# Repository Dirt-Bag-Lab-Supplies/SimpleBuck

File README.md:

# SimpleBuck
Simple buck-converter with selectable output voltage and current.

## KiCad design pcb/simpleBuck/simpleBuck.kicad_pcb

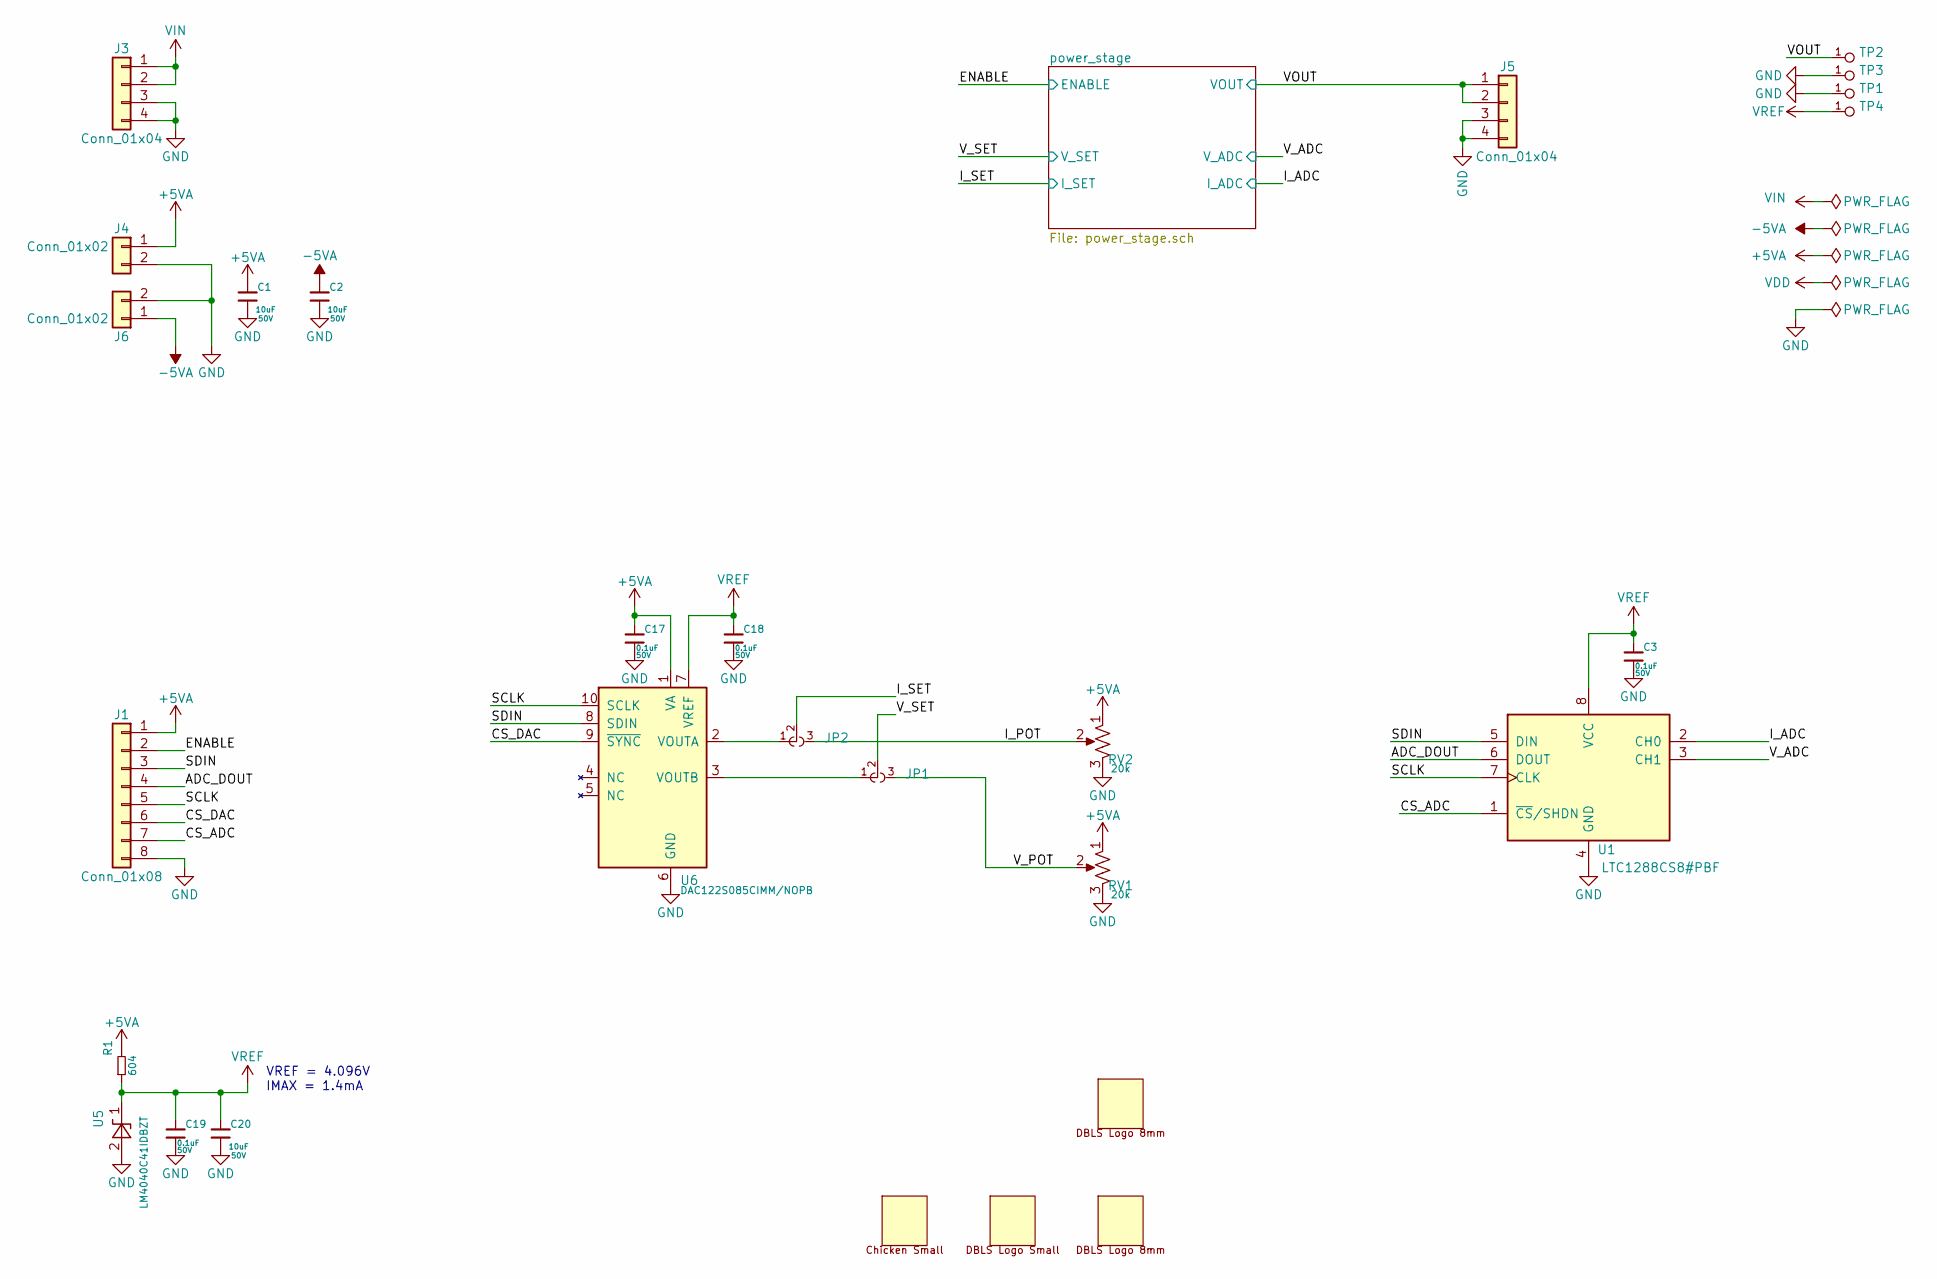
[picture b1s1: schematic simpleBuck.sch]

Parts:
C1, C2, C20: MURATA_GRT31CR61H106KE01L; C_1206; voltage 50V; mfg_pn GRT31CR61H106KE01L
C3, C17, C18, C19: MURATA_GCJ188R91H104KA01D; C_0603; voltage 50V; mfg_pn GCJ188R91H104KA01D
J1: Conn_01x08; Pin_Header_Straight_1x08_Pitch2.54mm
J3, J5: Conn_01x04; Pin_Header_Straight_1x04_Pitch2.54mm
J4, J6: Conn_01x02; Pin_Header_Straight_1x02_Pitch2.54mm
JP1, JP2: PAD_JUMPER_3PIN_12_NC_BY_TRACE
LOGO1: DBLS_Chicken_Small; Rooster_4mmx4mm
LOGO2: DBLS_van_logo_small_v1; van_logo_small
LOGO3: DBLS_van_logo_8mmX6mm; van_logo_8mmX6mm
LOGO4: DBLS_van_logo_8mmX6mm_mirror; van_logo_8mmX6mm_mirror
R1: VISHAYDALE_CRCW0603604RFKEAHP; R_0603; mfg_pn CRCW0603604RFKEAHP
RV1, RV2: BOURNS_PV37W203C01B00; Potentiometer_Trimmer_Bourns_3299Y; mfg_pn PV37W203C01B00
TP1, TP2, TP3, TP4: DBLS_TESTPOINT_NORMAL; DBLS_Testpoint_Normal
U1: ANALOG_LTC1288CS8#PBF; SOIC-8_3.9x4.9mm_Pitch1.27mm; mfg_pn LTC1288CS8#PBF
U5: TI_LM4040C41IDBZT; SOT-23; mfg_pn LM4040C41IDBZT
U6: TI_DAC122S085CIMM_NOPB; MSOP-10_3x3mm_Pitch0.5mm; mfg_pn DAC122S085CIMM/NOPB

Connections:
+5VA: C1.1, C17.1, J1.1, J4.1, R1.2, RV1.1, RV2.1, U6.1 (VA); also elsewhere on the board
-5VA: C2.1, J6.1; also elsewhere on the board
/ADC_DOUT: J1.4, U1.6 (DOUT)
/CS_ADC: J1.7, U1.1 (~CS~/SHDN)
/CS_DAC: J1.6, U6.9 (~SYNC)
/ENABLE: J1.2; also elsewhere on the board
/I_ADC: U1.2 (CH0); also elsewhere on the board
/I_POT: JP2.3, RV2.2
/I_SET: JP2.2; also elsewhere on the board
/SCLK: J1.5, U1.7 (CLK), U6.10 (SCLK)
/SDIN: J1.3, U1.5 (DIN), U6.8 (SDIN)
/VOUT: J5.1, J5.2, TP2.1; also elsewhere on the board
/V_ADC: U1.3 (CH1); also elsewhere on the board
/V_POT: JP1.3, RV1.2
/V_SET: JP1.2; also elsewhere on the board
GND: C1.2, C2.2, C3.2, C17.2, C18.2, C19.2, C20.2, J1.8, J3.3, J3.4, J4.2, J5.3, J5.4, J6.2, RV1.3, RV2.3, TP1.1, TP3.1, U1.4 (GND), U5.2 (A), U6.6 (GND); also elsewhere on the board
unnamed: JP1.1, U6.3 (VOUTB)
unnamed: JP2.1, U6.2 (VOUTA)
VIN: J3.1, J3.2; also elsewhere on the board
VREF: C3.1, C18.1, C19.1, C20.1, R1.1, TP4.1, U1.8 (VCC), U5.1 (K), U6.7 (VREF)

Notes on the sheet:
VREF = 4.096V IMAX = 1.4mA

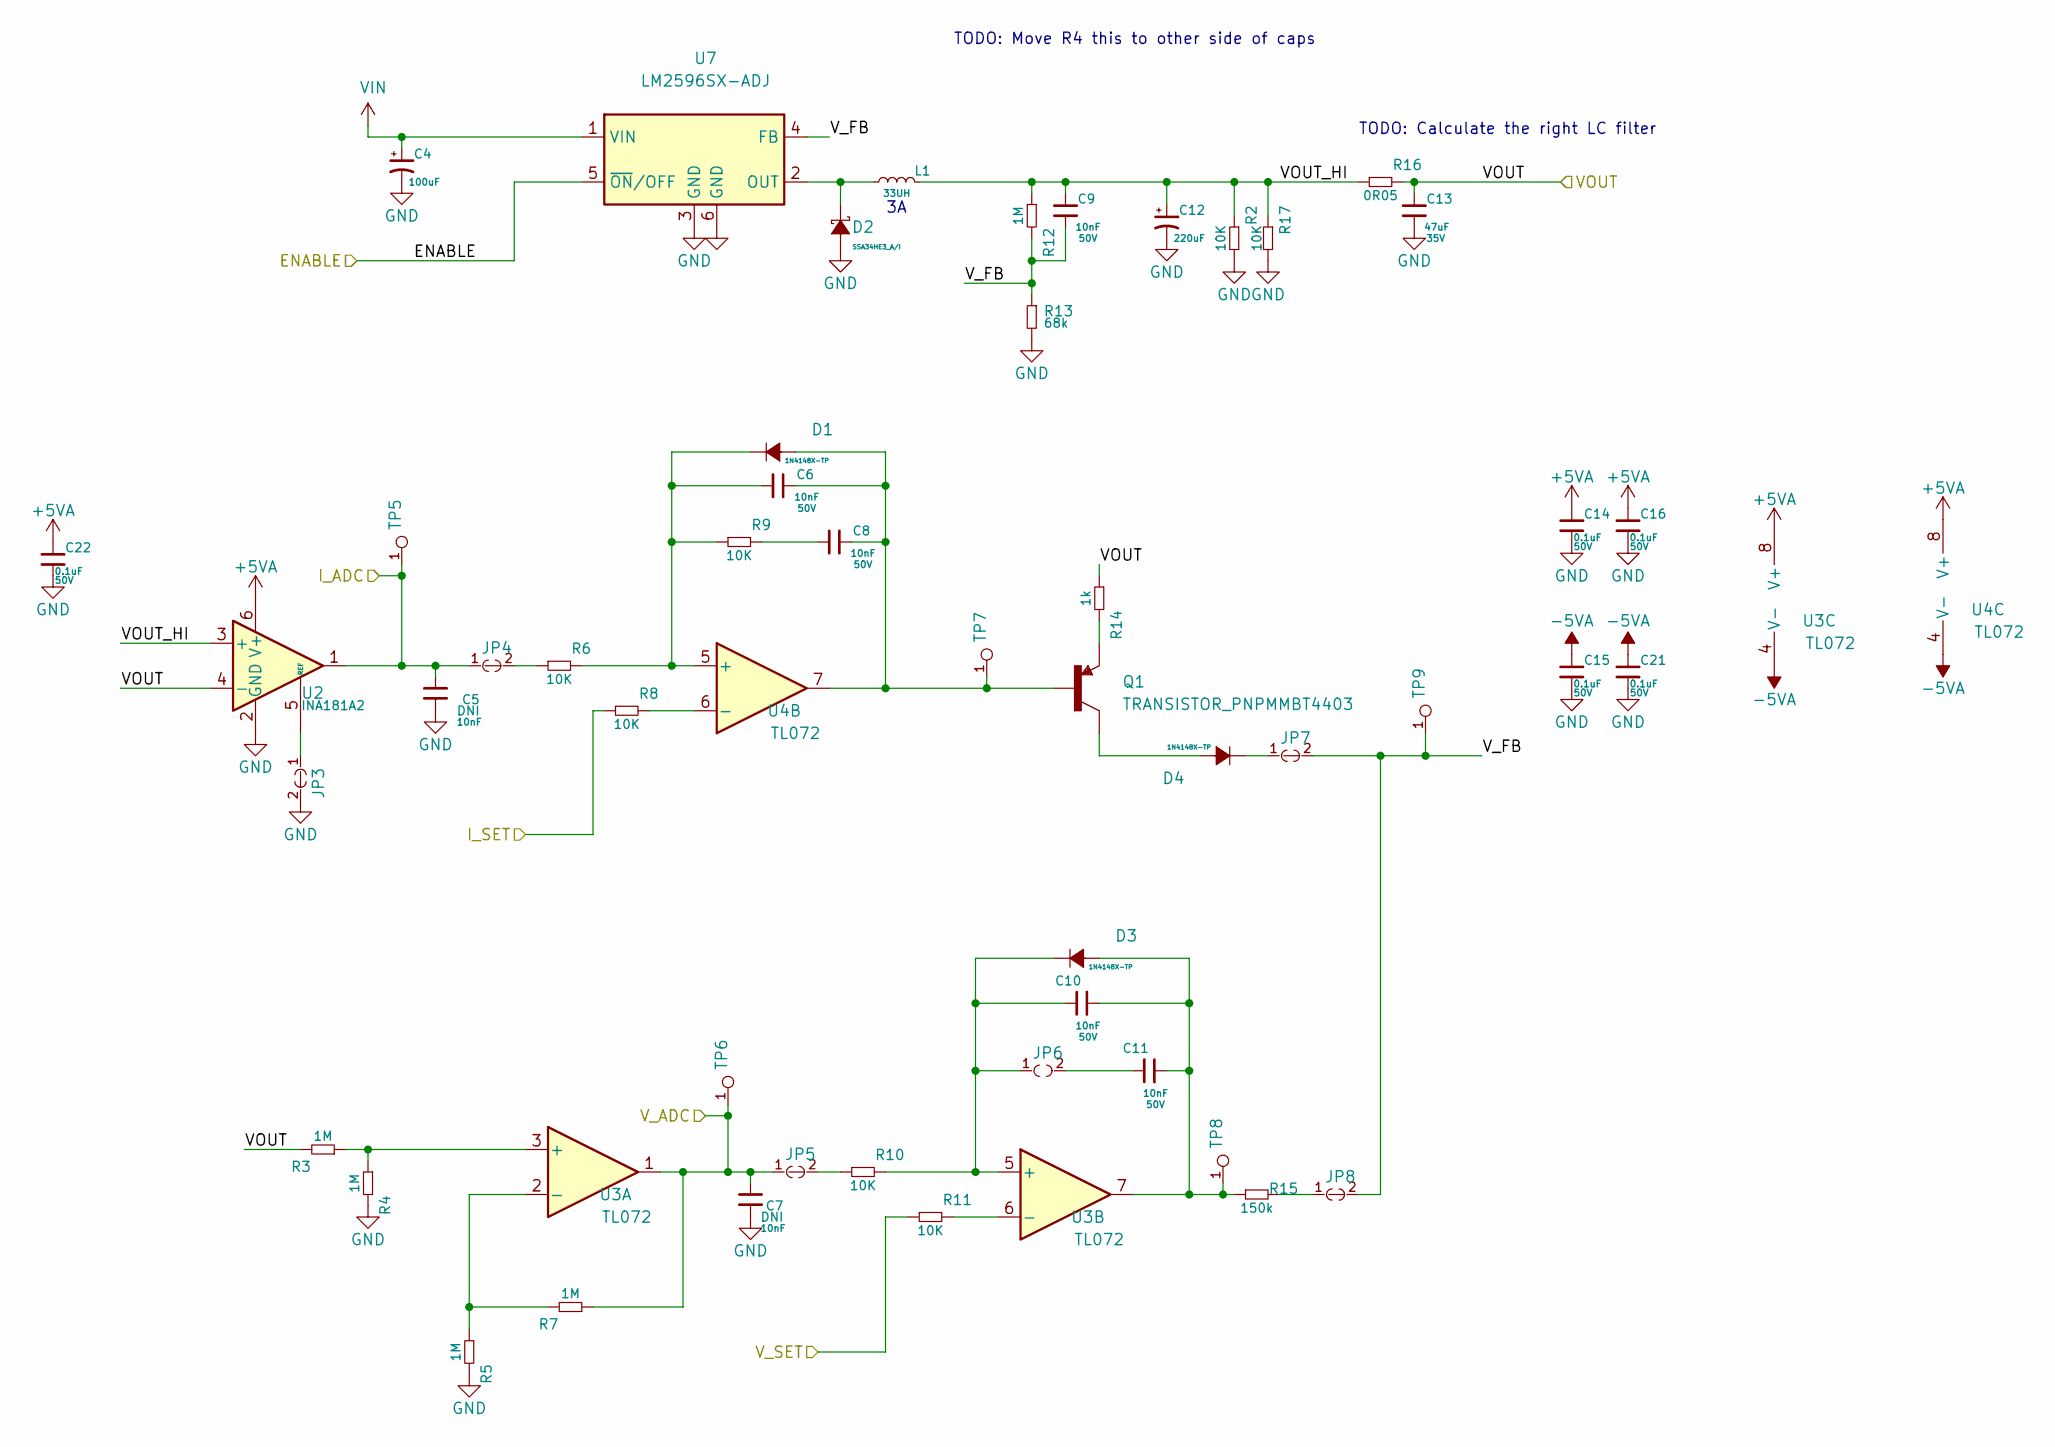
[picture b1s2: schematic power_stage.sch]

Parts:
C4: RUBYCON_100ZLH100MEFC10X20; CP_Radial_D10.0mm_P5.00mm; mfg_pn 100ZLH100MEFC10X20
C5, C6, C7, C8, C9, C10, C11: KEMET_C0603C103K5RAL7867; C_0603; voltage 50V; mfg_pn C0603C103K5RAL7867
C12: PANASONIC_EEU-FC1H221B; CP_Radial_D10.0mm_P5.00mm; mfg_pn EEU-FC1H221B
C13: MURATA_KRM55WR7YA476MH01L; C_2220; voltage 35V; mfg_pn KRM55WR7YA476MH01L
C14, C15, C16, C21, C22: MURATA_GCJ188R91H104KA01D; C_0603; voltage 50V; mfg_pn GCJ188R91H104KA01D
D1, D3, D4: MICRO_COMMERCIAL_1N4148X-TP; LED_0603; mfg_pn 1N4148X-TP
D2: VISHAY_SSA34HE3_A_I; D_SMA; mfg_pn SSA34HE3_A/I
JP3, JP4, JP5, JP7, JP8: PAD_JUMPER_2PIN_NC_BY_TRACE
JP6: PAD_JUMPER_2PIN_NO; PAD_JUMPER_2PIN_NO_0603
L1: BOURNS_SRR1260A-330M; L_12x12mm_h8mm; mfg_pn SRR1260A-330M
Q1: TRANSISTOR_PNPMMBT4403; SOT-23
R2, R6, R8, R9, R10, R11, R17: VISHAY_CRCW060310K0FKEBC; R_0603; mfg_pn CRCW060310K0FKEBC
R3, R4, R5, R7, R12: VISHAYDALE_CRCW06031M00FKEAC; R_0603; mfg_pn CRCW06031M00FKEAC
R13: VISHAYDALE_CRCW060368K0FKEA; R_0603; mfg_pn CRCW060368K0FKEA
R14: SMD-RES-1.0K-0603; R_0603; mfg_pn ESR03EZPF1001
R15: VISHAYDALE_CRCW0603150KFKEAC; R_0603; mfg_pn CRCW0603150KFKEAC
R16: STACKPOLE_CSRT2512FT50L0-UP; R_2512; mfg_pn CSRT2512FT50L0-UP
TP5, TP6, TP7, TP8, TP9: DBLS_TESTPOINT_NORMAL; DBLS_Testpoint_Normal
U2: TI_INA181A2; SOT-23-6; mfg_pn INA181A2IDBVT
U3, U4: TI_TL072HIDBVR; SOIC-8_3.9x4.9mm_Pitch1.27mm; mfg_pn TL072HIDBVR
U7: NATIONALSEMI_LM2596SX-ADJ; TO-263-5_TabPin6; mfg_pn LM2596SX-ADJ

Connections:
+5VA: C14.1, C16.1, C22.1, U2.6 (V+), U3.8 (V+), U4.8 (V+); also elsewhere on the board
-5VA: C15.1, C21.1, U3.4 (V-), U4.4 (V-); also elsewhere on the board
/ENABLE: U7.5 (~ON~/OFF); also elsewhere on the board
/I_ADC: C5.2, JP4.1, TP5.1, U2.1; also elsewhere on the board
/I_SET: R8.1; also elsewhere on the board
/VOUT: C13.1, R3.2, R14.1, R16.2, U2.4 (-); also elsewhere on the board
/V_ADC: C7.2, JP5.1, R7.1, TP6.1, U3.1; also elsewhere on the board
/V_SET: R11.1; also elsewhere on the board
/power_stage/VOUT_HI: C9.1, C12.1, L1.2, R2.1, R12.1, R16.1, R17.1, U2.3 (+)
/power_stage/V_FB: C9.2, JP7.2, JP8.2, R12.2, R13.1, TP9.1, U7.4 (FB)
GND: C4.2, C5.1, C7.1, C12.2, C13.2, C14.2, C15.2, C16.2, C21.2, C22.2, D2.2 (A), JP3.2, R2.2, R4.2, R5.2, R13.2, R17.2, U2.2 (GND), U7.3 (GND), U7.6 (GND); also elsewhere on the board
unnamed: C6.1, C8.1, D1.2 (A), Q1.1 (B), TP7.1, U4.7
unnamed: C6.2, D1.1 (K), R6.2, R9.1, U4.5 (+)
unnamed: C8.2, R9.2
unnamed: C10.1, C11.1, D3.2 (A), R15.1, TP8.1, U3.7
unnamed: C10.2, D3.1 (K), JP6.1, R10.2, U3.5 (+)
unnamed: C11.2, JP6.2
unnamed: D2.1 (K), L1.1, U7.2 (OUT)
unnamed: D4.1 (K), JP7.1
unnamed: D4.2 (A), Q1.3 (C)
unnamed: JP3.1, U2.5 (REF)
unnamed: JP4.2, R6.1
unnamed: JP5.2, R10.1
unnamed: JP8.1, R15.2
unnamed: Q1.2 (E), R14.2
unnamed: R3.1, R4.1, U3.3 (+)
unnamed: R5.1, R7.2, U3.2 (-)
unnamed: R8.2, U4.6 (-)
unnamed: R11.2, U3.6 (-)
VIN: C4.1, U7.1 (VIN); also elsewhere on the board

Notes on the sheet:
TODO: Calculate the right LC filter
TODO: Move R4 this to other side of caps

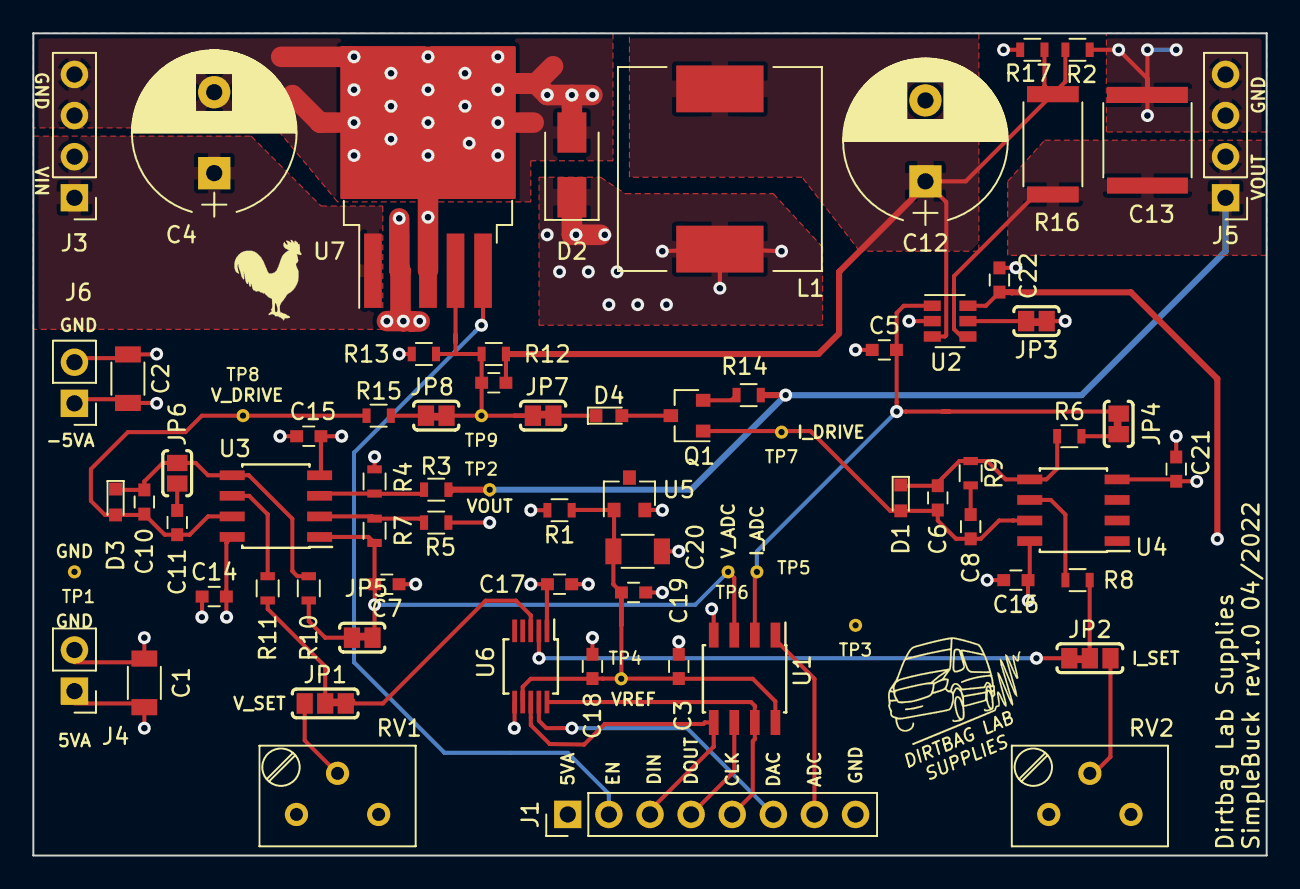
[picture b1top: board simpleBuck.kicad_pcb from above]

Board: 4 copper layers, 76.2 x 50.8 mm, 79 parts (1 on the bottom side), 40 nets.

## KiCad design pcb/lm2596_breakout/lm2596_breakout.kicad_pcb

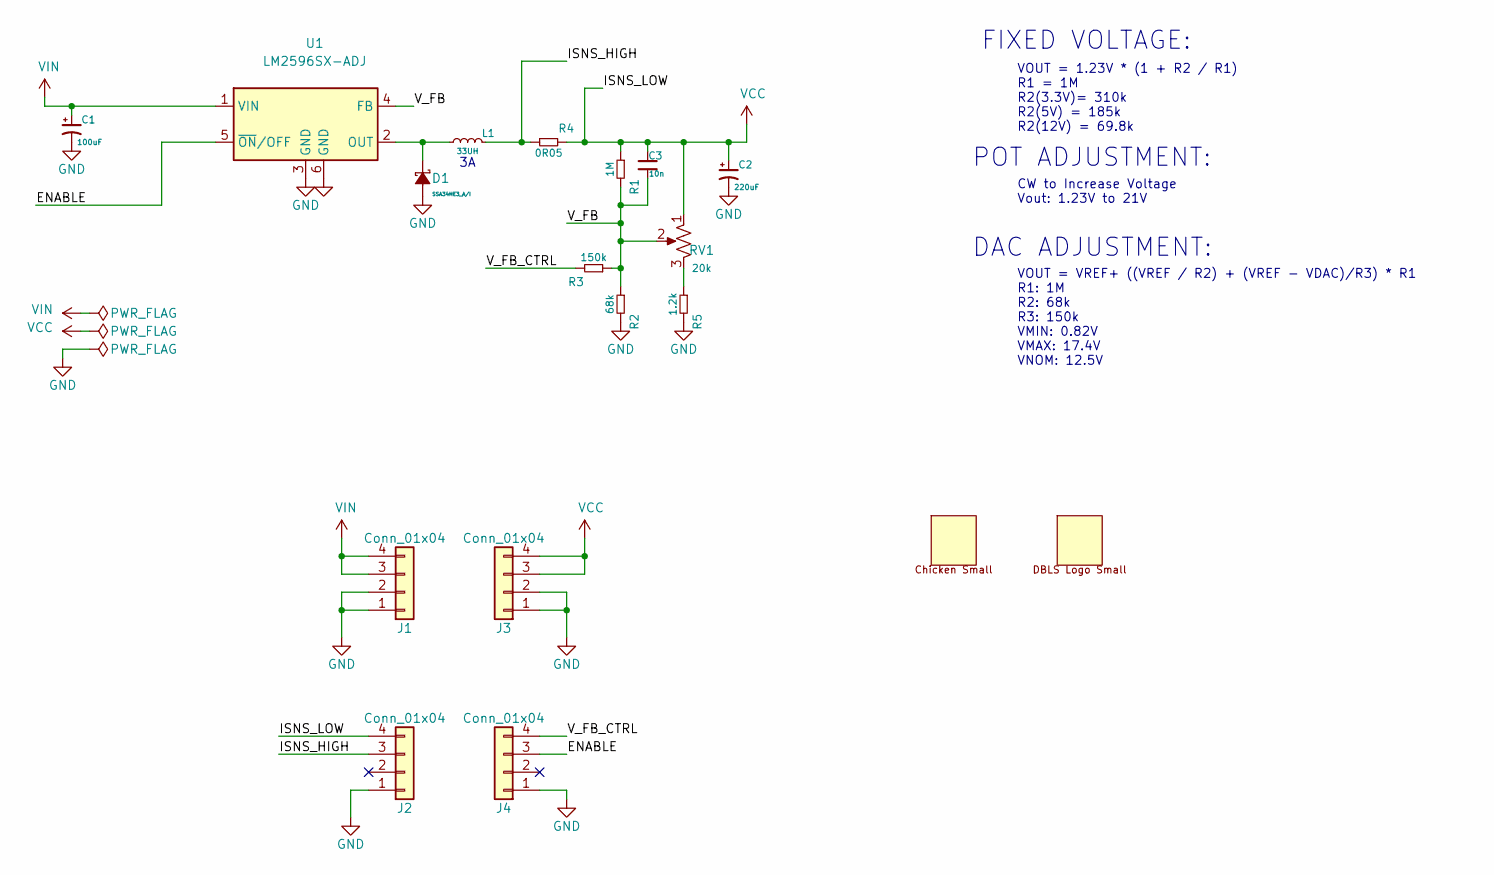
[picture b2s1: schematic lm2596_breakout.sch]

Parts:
C1: RUBYCON_100ZLH100MEFC10X20; CP_Radial_D10.0mm_P5.00mm; mfg_pn 100ZLH100MEFC10X20
C2: PANASONIC_EEU-FC1H221B; CP_Radial_D10.0mm_P5.00mm; mfg_pn EEU-FC1H221B
C3: MURATA_GCM155R71E103KA37D; C_0402; mfg_pn GCM155R71E103KA37D
D1: VISHAY_SSA34HE3_A_I; D_SMA; mfg_pn SSA34HE3_A/I
J1, J2, J3, J4: Conn_01x04; Pin_Header_Straight_1x04_Pitch2.54mm
L1: BOURNS_SRR1260A-330M; L_12x12mm_h8mm; mfg_pn SRR1260A-330M
LOGO1: DBLS_Chicken_Small; Rooster_4mmx4mm
LOGO2: DBLS_van_logo_small_v1; van_logo_small
R1: VISHAYDALE_CRCW04021M00FKEDC; R_0402; mfg_pn CRCW04021M00FKEDC
R2: VISHAYDALE_CRCW040268K0FKEDC; R_0402; mfg_pn CRCW040268K0FKEDC
R3: VISHAYDALE_CRCW0402150KFKEDC; R_0402; mfg_pn CRCW0402150KFKEDC
R4: STACKPOLE_CSRT2512FT50L0-UP; R_2512; mfg_pn CSRT2512FT50L0-UP
R5: VISHAYDALE_CRCW06031K20FKEAC; R_0603; mfg_pn CRCW06031K20FKEAC
RV1: BOURNS_PV37W203C01B00; Potentiometer_Trimmer_Bourns_3299Y; mfg_pn PV37W203C01B00
U1: NATIONALSEMI_LM2596SX-ADJ; TO-263-5_TabPin6; mfg_pn LM2596SX-ADJ

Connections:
/ENABLE: J4.3, U1.5 (~ON~/OFF)
/ISNS_HIGH: J2.3, L1.2, R4.1
/V_FB: C3.2, R1.2, R2.1, R3.1, RV1.2, U1.4 (FB)
/V_FB_CTRL: J4.4, R3.2
GND: C1.2, C2.2, D1.2 (A), J1.1, J1.2, J2.1, J3.1, J3.2, J4.1, R2.2, R5.2, U1.3 (GND), U1.6 (GND)
unnamed: D1.1 (K), L1.1, U1.2 (OUT)
unnamed: R5.1, RV1.3
VCC: C2.1, C3.1, J2.4, J3.3, J3.4, R1.1, R4.2, RV1.1
VIN: C1.1, J1.3, J1.4, U1.1 (VIN)

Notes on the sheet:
VOUT = 1.23V * (1 + R2 / R1) R1 = 1M R2(3.3V)= 310k R2(5V) = 185k R2(12V) = 69.8k
CW to Increase Voltage Vout: 1.23V to 21V
FIXED VOLTAGE:
POT ADJUSTMENT:
DAC ADJUSTMENT:
VOUT = VREF+ ((VREF / R2) + (VREF - VDAC)/R3) * R1 R1: 1M R2: 68k R3: 150k VMIN: 0.82V VMAX: 17.4V VNOM: 12.5V

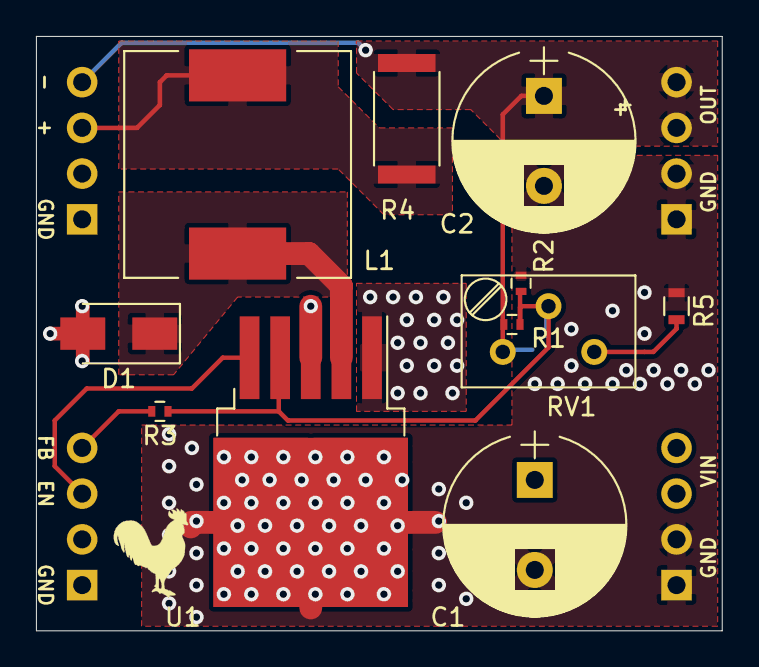
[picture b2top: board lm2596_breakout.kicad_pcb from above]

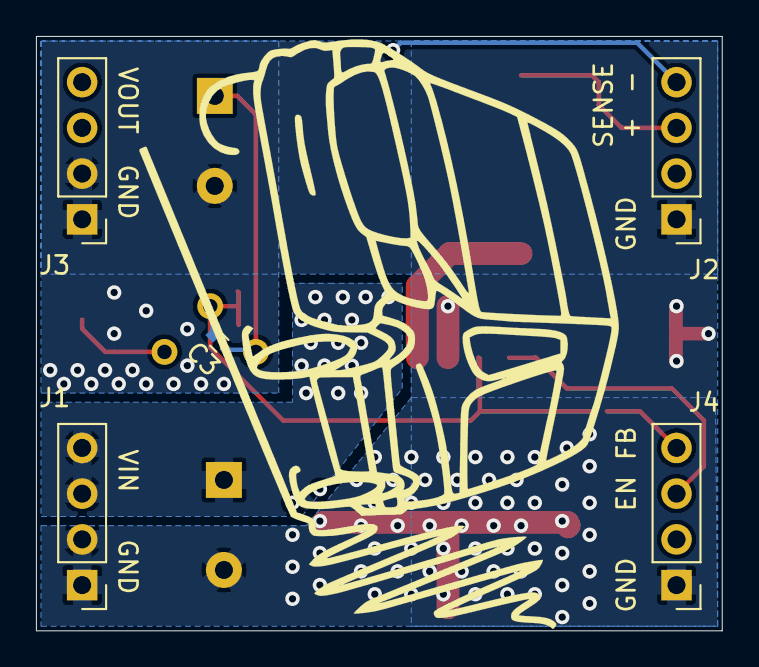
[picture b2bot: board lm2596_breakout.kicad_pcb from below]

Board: 2 copper layers, 38.1 x 33.0 mm, 18 parts (6 on the bottom side), 9 nets.

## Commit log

2020-11-01 Schematic draft
2022-02-01 Made lm2596 breakout board.
2022-02-07 Rough layout + silkscreen.
2022-02-08 layout + bom completed.
2022-02-16 v1 - placed order with OSH park
2022-04-14 Added lm2596 and DACS + prelim layout.
2022-04-16 Updated schematic to include lm2596 on board.
2022-04-17 Added jumpers and finalized DAC/ADC selection.
2022-04-17 Prelim Layout before silkscreen tuning.
2022-04-17 Finished layout. Heading to fab
2022-04-18 Minor movement of text
